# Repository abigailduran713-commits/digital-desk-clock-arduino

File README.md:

# Arduino Digital Desk Clock

## Project Overview
This project is a standalone digital desk clock built using an Arduino Uno, a DS3231 real-time clock module, and a 16x2 LCD.

The clock features a three-button menu system, user-adjustable time settings, interval-based reminders, and a visual LED alert. A DS3231 RTC provides accurate timekeeping, while non-blocking timing allows the system to remain responsive while handling user input, display updates, and reminders.

After testing the circuit on a breadboard, the complete system was converted into a custom PCB designed in KiCad. The PCB has been designed and is currently awaiting fabrication and assembly.

## Features
- 16x2 LCD display
- Time and date display
- Accurate timekeeping using a DS3231 RTC module
- User-adjustable time through the LCD menu
- Menu navigation using three push buttons: UP, DOWN, and MODE
- Interval-based reminders
- Enable and disable reminder settings
- Blinking LED alert during active reminders
- Custom PCB designed in KiCad

## Hardware Used 

### Breadboard Prototype
- Arduino Uno R3
- 16x2 LCD display
- DS3231 Real-time clock module
- Push buttons (x3)
- LED + resistor
- Potentiometer (LCD contrast)
- Breadboard and jumper wires

### PCB Version
- Custom PCB designed in KiCad
- Arduino Uno R3 and headers
- RTC module and headers
- LCD module and headers
- Push-button inputs
- LED + resistors
- Potentiometer

## How It Works
The DS3231 real-time clock module maintains the current time independently of the Arduino. The Arduino reads the time from the RTC through I2C communication and displays it on the 16x2 LCD.

The user interacts with the clock through three push buttons. A menu-driven state machine allows the buttons to perform different actions depending on the active screen, including navigating settings, changing the displayed time, selecting reminder intervals, and enabling or disabling reminders.

Reminder timing is handled without long blocking delays. The program uses `millis()` to manage LCD updates, button input, reminder checks, and the blinking LED alert while keeping the system responsive.

The circuit was initially developed and tested on a breadboard. After confirming the main hardware and software functions, the schematic and PCB layout were created in KiCad for a more permanent version of the project.

## PCB Design
After completing the breadboard prototype, the circuit was recreated as a schematic in KiCad and converted into a custom PCB layout.

The design process included:
- Assignming schematic symbols and footprints
- Running electrical rules checks
- Definin the board outline
- Placing components
- Routing signal and power traces
- Adding a ground plane
- Running design rules checks
- Generating Gerber and drill files for fabrication

## Future Improvements
- Fabricate and assemble the custom PCB
- Test and validate the assembled board
- Design a compact enclosure
- Revise the PCB if issues are found during physical testing

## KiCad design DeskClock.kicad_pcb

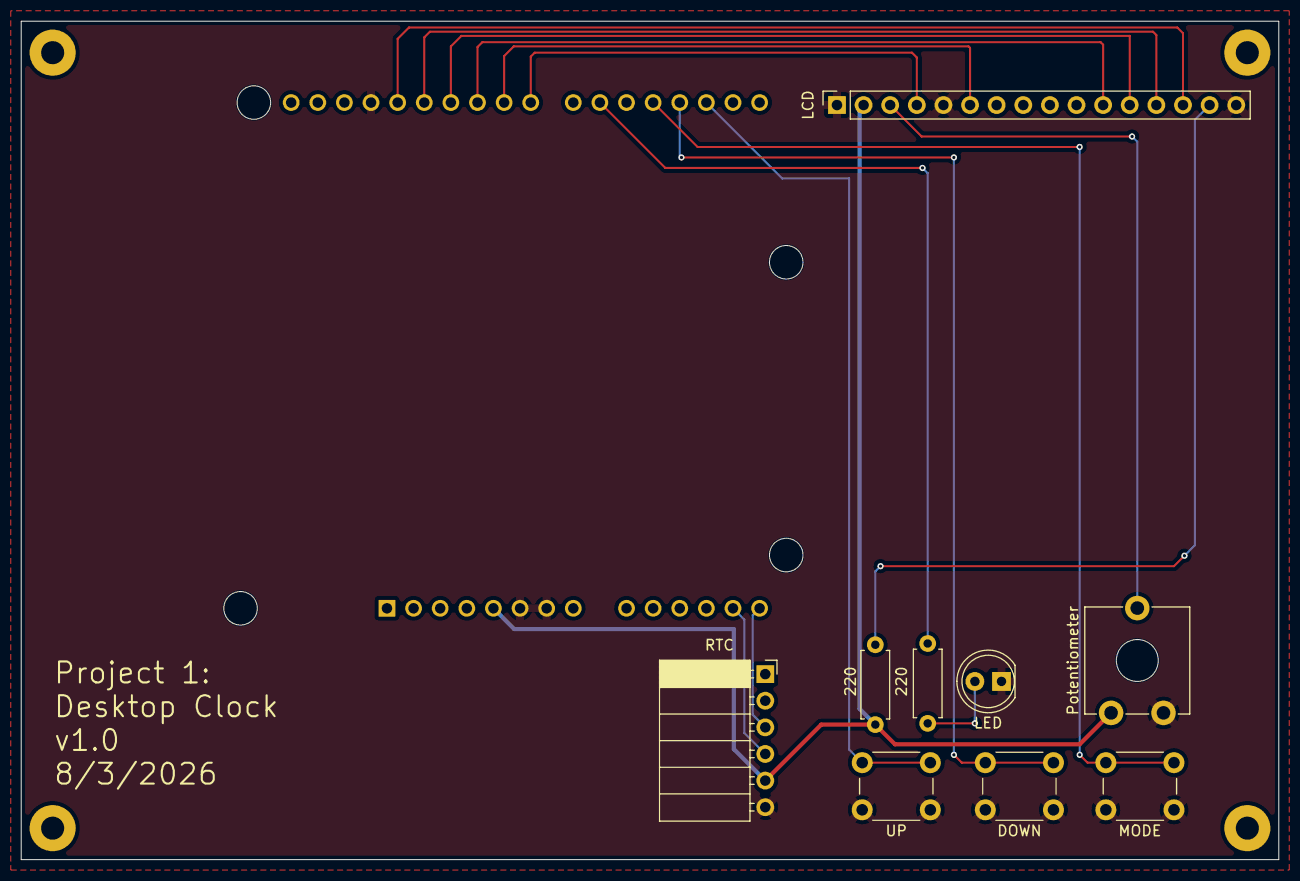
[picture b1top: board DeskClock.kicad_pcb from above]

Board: 2 copper layers, 120.0 x 80.0 mm, 14 parts (1 on the bottom side), 17 nets.

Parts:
220: 220; R_Axial_DIN0207_L6.3mm_D2.5mm_P7.62mm_Horizontal
ARDUINO UNO R3: Arduino_UNO_R3; Arduino_UNO_R3_WithMountingHoles
DOWN: DOWN; SW_PUSH_6mm_H8.5mm
H1, H2, H3, H4: MountingHole; MountingHole_2.2mm_M2_Pad
LCD: Conn_01x16_PinLCD; PinSocket_1x16_P2.54mm_Vertical
LED: LED; LED_D5.0mm
MODE: MODE; SW_PUSH_6mm_H8.5mm
Potentiometer: R_Potentiometer; Potentiometer_ACP_CA9-V10_Vertical_Hole
R1: 220; R_Axial_DIN0207_L6.3mm_D2.5mm_P7.62mm_Horizontal
RTC: Conn_01x06_PinRTC; PinSocket_1x06_P2.54mm_Horizontal
UP: UP; SW_PUSH_6mm_H8.5mm

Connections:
GND: ARDUINO UNO R3.6 (GND), ARDUINO UNO R3.7 (GND), ARDUINO UNO R3.29 (GND), DOWN.1, LCD.1, LCD.5, LCD.16, LED.1 (K), MODE.1, Potentiometer.1, RTC.6, UP.1
unnamed: 220.1, ARDUINO UNO R3.5 (+5V), LCD.2, Potentiometer.3, RTC.5
unnamed: ARDUINO UNO R3.17 (D2), UP.2
unnamed: ARDUINO UNO R3.18 (D3), DOWN.2
unnamed: ARDUINO UNO R3.19 (D4), MODE.2
unnamed: ARDUINO UNO R3.21 (D6), R1.1
unnamed: ARDUINO UNO R3.23 (D8), LCD.4
unnamed: ARDUINO UNO R3.24 (D9), LCD.6
unnamed: ARDUINO UNO R3.25 (D10), LCD.11
unnamed: ARDUINO UNO R3.26 (D11), LCD.12
unnamed: ARDUINO UNO R3.27 (D12), LCD.13
unnamed: ARDUINO UNO R3.28 (D13), LCD.14
unnamed: LED.2 (A), R1.2
unnamed: ARDUINO UNO R3.14 (SCL/A5), RTC.3
unnamed: ARDUINO UNO R3.13 (SDA/A4), RTC.4
unnamed: LCD.3, Potentiometer.2
unnamed: 220.2, LCD.15
